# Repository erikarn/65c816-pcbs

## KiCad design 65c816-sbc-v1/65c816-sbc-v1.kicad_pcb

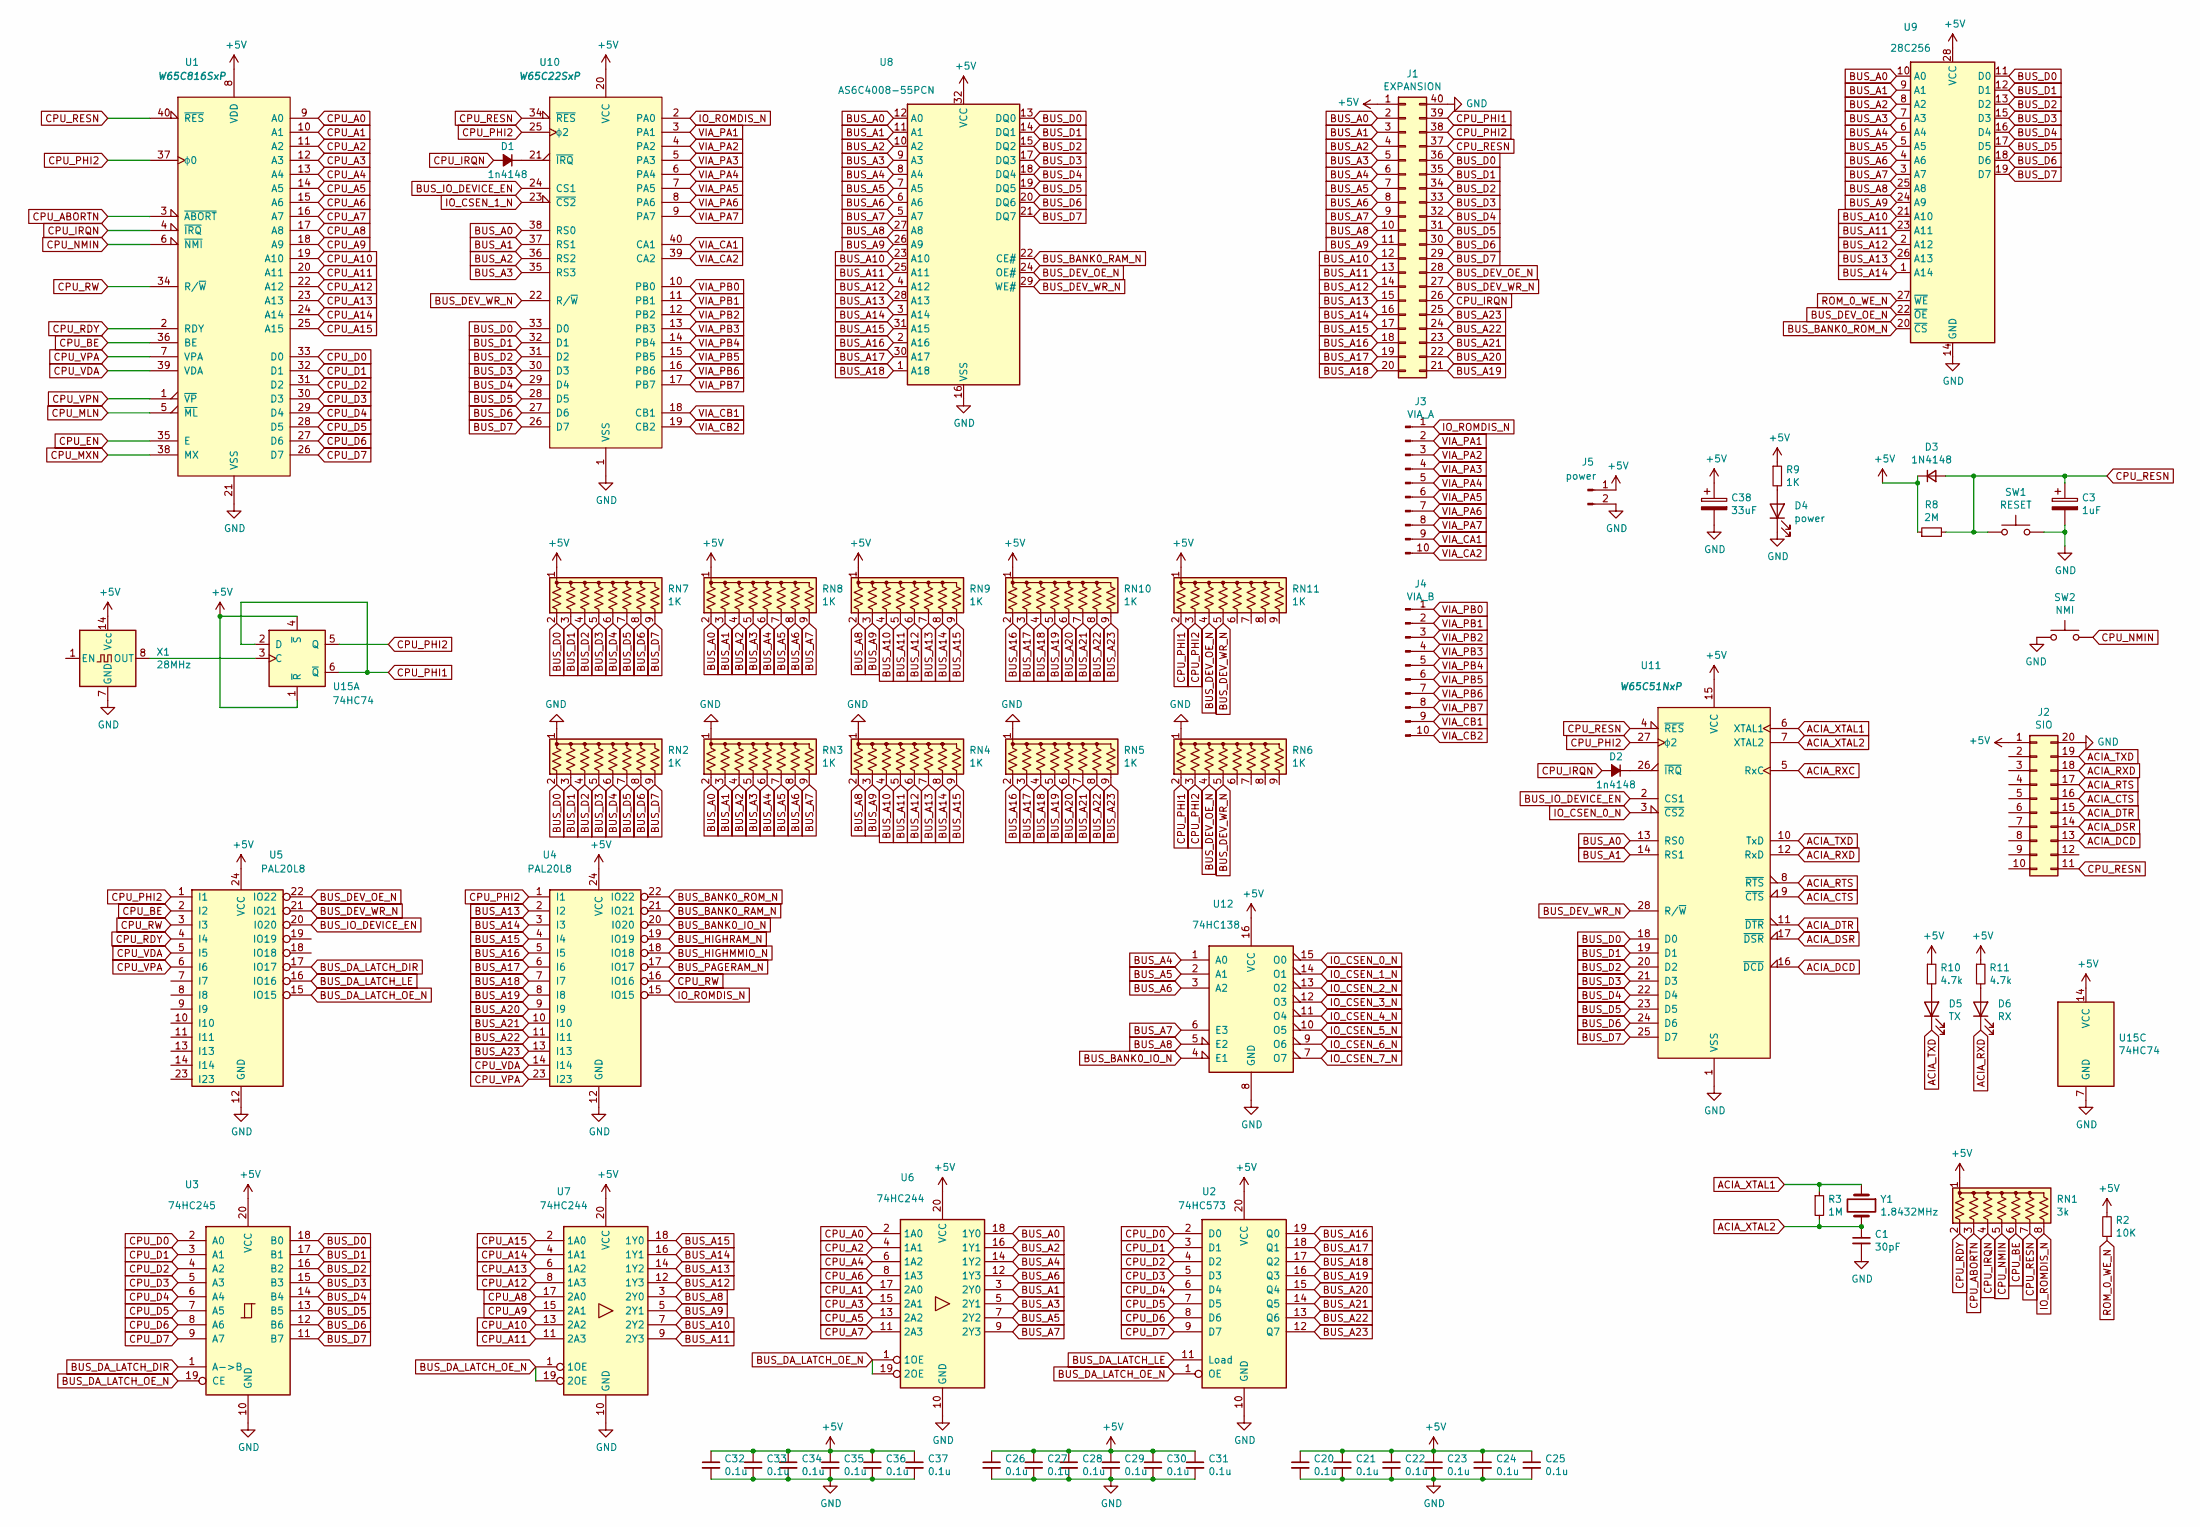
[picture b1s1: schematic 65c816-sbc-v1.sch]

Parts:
C1: 30pF; C_Rect_L4.0mm_W2.5mm_P2.50mm
C3: 1uF; CP_Radial_D6.3mm_P2.50mm
C20, C21, C22, C23, C24, C25, C26, C27, C28, C29, C30, C31, C32, C33, C34, C35, C36, C37: 0.1u; C_Rect_L4.0mm_W2.5mm_P2.50mm
C38: 33uF; CP_Radial_D6.3mm_P2.50mm
D1, D2: 1n4148; D_DO-35_SOD27_P7.62mm_Horizontal
D3: 1N4148; D_DO-35_SOD27_P7.62mm_Horizontal
D4: power; LED_D4.0mm
D5: TX; LED_D4.0mm
D6: RX; LED_D4.0mm
J1: EXPANSION; PinHeader_2x20_P2.54mm_Vertical
J2: SIO; PinHeader_2x10_P2.54mm_Vertical
J3: VIA_A; PinHeader_1x10_P2.54mm_Vertical
J4: VIA_B; PinHeader_1x10_P2.54mm_Vertical
J5: power; PinHeader_1x02_P2.54mm_Vertical
R2: 10K; R_Axial_DIN0207_L6.3mm_D2.5mm_P5.08mm_Vertical
R3: 1M; R_Axial_DIN0207_L6.3mm_D2.5mm_P5.08mm_Vertical
R8: 2M; R_Axial_DIN0207_L6.3mm_D2.5mm_P5.08mm_Vertical
R9: 1K; R_Axial_DIN0207_L6.3mm_D2.5mm_P5.08mm_Vertical
R10, R11: 4.7k; R_Axial_DIN0207_L6.3mm_D2.5mm_P5.08mm_Vertical
RN1: 3k; R_Array_SIP8
RN2, RN3, RN4, RN5, RN6, RN7, RN8, RN9, RN10, RN11: 1K; R_Array_SIP9
SW1: RESET; KSA_Tactile_SPST
SW2: NMI; KSA_Tactile_SPST
U1: W65C816SxP; DIP-40_W15.24mm_Socket
U2: 74HC573; DIP-20_W7.62mm_Socket
U3: 74HC245; DIP-20_W7.62mm_Socket
U4, U5: PAL20L8; DIP-24_W7.62mm_Socket
U6, U7: 74HC244; DIP-20_W7.62mm_Socket
U8: AS6C4008-55PCN; DIP-32_W15.24mm
U9: 28C256; DIP-28_W15.24mm_Socket
U10: W65C22SxP; DIP-40_W15.24mm_Socket
U11: W65C51NxP; DIP-40_W15.24mm_Socket
U12: 74HC138; DIP-16_W7.62mm_Socket
U15: 74HC74; DIP-14_W7.62mm_Socket
X1: 28MHz; Oscillator_DIP-14
Y1: 1.8432MHz; Crystal_HC49-4H_Vertical

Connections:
+5V: C20.1, C21.1, C22.1, C23.1, C24.1, C25.1, C26.1, C27.1, C28.1, C29.1, C30.1, C31.1, C32.1, C33.1, C34.1, C35.1, C36.1, C37.1, C38.1, D3.1 (K), J1.1, J2.1, J5.1, R2.2, R8.1, R9.1, R10.1, R11.1, RN1.1 (common), RN7.1 (common), RN8.1 (common), RN9.1 (common), RN10.1 (common), RN11.1 (common), U1.8 (VDD), U2.20 (VCC), U3.20 (VCC), U4.24 (VCC), U5.24 (VCC), U6.20 (VCC), U7.20 (VCC), U8.32 (VCC), U9.28 (VCC), U10.20 (VCC), U11.15 (VCC), U12.16 (VCC), U15.1 (~R), U15.4 (~S), U15.14 (VCC), X1.14 (Vcc)
ACIA_CTS: J2.16, U11.9 (~CTS)
ACIA_DCD: J2.13, U11.16 (~DCD)
ACIA_DSR: J2.14, U11.17 (~DSR)
ACIA_DTR: J2.15, U11.11 (~DTR)
ACIA_RTS: J2.17, U11.8 (~RTS)
ACIA_RXC: U11.5 (RxC)
ACIA_RXD: D6.1 (K), J2.18, U11.12 (RxD)
ACIA_TXD: D5.1 (K), J2.19, U11.10 (TxD)
ACIA_XTAL1: R3.1, U11.6 (XTAL1), Y1.1
ACIA_XTAL2: C1.1, R3.2, U11.7 (XTAL2), Y1.2
BUS_A0: J1.2, RN3.2 (R1), RN8.2 (R1), U6.18 (1Y0), U8.12 (A0), U9.10 (A0), U10.38 (RS0), U11.13 (RS0)
BUS_A1: J1.3, RN3.3 (R2), RN8.3 (R2), U6.3 (2Y0), U8.11 (A1), U9.9 (A1), U10.37 (RS1), U11.14 (RS1)
BUS_A2: J1.4, RN3.4 (R3), RN8.4 (R3), U6.16 (1Y1), U8.10 (A2), U9.8 (A2), U10.36 (RS2)
BUS_A3: J1.5, RN3.5 (R4), RN8.5 (R4), U6.5 (2Y1), U8.9 (A3), U9.7 (A3), U10.35 (RS3)
BUS_A4: J1.6, RN3.6 (R5), RN8.6 (R5), U6.14 (1Y2), U8.8 (A4), U9.6 (A4), U12.1 (A0)
BUS_A5: J1.7, RN3.7 (R6), RN8.7 (R6), U6.7 (2Y2), U8.7 (A5), U9.5 (A5), U12.2 (A1)
BUS_A6: J1.8, RN3.8 (R7), RN8.8 (R7), U6.12 (1Y3), U8.6 (A6), U9.4 (A6), U12.3 (A2)
BUS_A7: J1.9, RN3.9 (R8), RN8.9 (R8), U6.9 (2Y3), U8.5 (A7), U9.3 (A7), U12.6 (E3)
BUS_A8: J1.10, RN4.2 (R1), RN9.2 (R1), U7.3 (2Y0), U8.27 (A8), U9.25 (A8), U12.5 (E2)
BUS_A9: J1.11, RN4.3 (R2), RN9.3 (R2), U7.5 (2Y1), U8.26 (A9), U9.24 (A9)
BUS_A10: J1.12, RN4.4 (R3), RN9.4 (R3), U7.7 (2Y2), U8.23 (A10), U9.21 (A10)
BUS_A11: J1.13, RN4.5 (R4), RN9.5 (R4), U7.9 (2Y3), U8.25 (A11), U9.23 (A11)
BUS_A12: J1.14, RN4.6 (R5), RN9.6 (R5), U7.12 (1Y3), U8.4 (A12), U9.2 (A12)
BUS_A13: J1.15, RN4.7 (R6), RN9.7 (R6), U4.2 (I2), U7.14 (1Y2), U8.28 (A13), U9.26 (A13)
BUS_A14: J1.16, RN4.8 (R7), RN9.8 (R7), U4.3 (I3), U7.16 (1Y1), U8.3 (A14), U9.1 (A14)
BUS_A15: J1.17, RN4.9 (R8), RN9.9 (R8), U4.4 (I4), U7.18 (1Y0), U8.31 (A15)
BUS_A16: J1.18, RN5.2 (R1), RN10.2 (R1), U2.19 (Q0), U4.5 (I5), U8.2 (A16)
BUS_A17: J1.19, RN5.3 (R2), RN10.3 (R2), U2.18 (Q1), U4.6 (I6), U8.30 (A17)
BUS_A18: J1.20, RN5.4 (R3), RN10.4 (R3), U2.17 (Q2), U4.7 (I7), U8.1 (A18)
BUS_A19: J1.21, RN5.5 (R4), RN10.5 (R4), U2.16 (Q3), U4.8 (I8)
BUS_A20: J1.22, RN5.6 (R5), RN10.6 (R5), U2.15 (Q4), U4.9 (I9)
BUS_A21: J1.23, RN5.7 (R6), RN10.7 (R6), U2.14 (Q5), U4.10 (I10)
BUS_A22: J1.24, RN5.8 (R7), RN10.8 (R7), U2.13 (Q6), U4.11 (I11)
BUS_A23: J1.25, RN5.9 (R8), RN10.9 (R8), U2.12 (Q7), U4.13 (I13)
BUS_BANK0_IO_N: U4.20 (I020), U12.4 (E1)
BUS_BANK0_RAM_N: U4.21 (IO21), U8.22 (CE#)
BUS_BANK0_ROM_N: U4.22 (IO22), U9.20 (~CS)
BUS_D0: J1.36, RN2.2 (R1), RN7.2 (R1), U3.18 (B0), U8.13 (DQ0), U9.11 (D0), U10.33 (D0), U11.18 (D0)
BUS_D1: J1.35, RN2.3 (R2), RN7.3 (R2), U3.17 (B1), U8.14 (DQ1), U9.12 (D1), U10.32 (D1), U11.19 (D1)
BUS_D2: J1.34, RN2.4 (R3), RN7.4 (R3), U3.16 (B2), U8.15 (DQ2), U9.13 (D2), U10.31 (D2), U11.20 (D2)
BUS_D3: J1.33, RN2.5 (R4), RN7.5 (R4), U3.15 (B3), U8.17 (DQ3), U9.15 (D3), U10.30 (D3), U11.21 (D3)
BUS_D4: J1.32, RN2.6 (R5), RN7.6 (R5), U3.14 (B4), U8.18 (DQ4), U9.16 (D4), U10.29 (D4), U11.22 (D4)
BUS_D5: J1.31, RN2.7 (R6), RN7.7 (R6), U3.13 (B5), U8.19 (DQ5), U9.17 (D5), U10.28 (D5), U11.23 (D5)
BUS_D6: J1.30, RN2.8 (R7), RN7.8 (R7), U3.12 (B6), U8.20 (DQ6), U9.18 (D6), U10.27 (D6), U11.24 (D6)
BUS_D7: J1.29, RN2.9 (R8), RN7.9 (R8), U3.11 (B7), U8.21 (DQ7), U9.19 (D7), U10.26 (D7), U11.25 (D7)
BUS_DA_LATCH_DIR: U3.1 (A->B), U5.17 (IO17)
BUS_DA_LATCH_LE: U2.11 (Load), U5.16 (IO16)
BUS_DA_LATCH_OE_N: U2.1 (OE), U3.19 (CE), U5.15 (IO15), U6.1 (1OE), U6.19 (2OE), U7.1 (1OE), U7.19 (2OE)
BUS_DEV_OE_N: J1.28, RN6.4 (R3), RN11.4 (R3), U5.22 (IO22), U8.24 (OE#), U9.22 (~OE)
BUS_DEV_WR_N: J1.27, RN6.5 (R4), RN11.5 (R4), U5.21 (IO21), U8.29 (WE#), U10.22 (R/~W), U11.28 (R/~W)
BUS_HIGHMMIO_N: U4.18 (IO18)
BUS_HIGHRAM_N: U4.19 (IO19)
BUS_IO_DEVICE_EN: U5.20 (I020), U10.24 (CS1), U11.2 (CS1)
BUS_PAGERAM_N: U4.17 (IO17)
CPU_A0: U1.9 (A0), U6.2 (1A0)
CPU_A1: U1.10 (A1), U6.17 (2A0)
CPU_A2: U1.11 (A2), U6.4 (1A1)
CPU_A3: U1.12 (A3), U6.15 (2A1)
CPU_A4: U1.13 (A4), U6.6 (1A2)
CPU_A5: U1.14 (A5), U6.13 (2A2)
CPU_A6: U1.15 (A6), U6.8 (1A3)
CPU_A7: U1.16 (A7), U6.11 (2A3)
CPU_A8: U1.17 (A8), U7.17 (2A0)
CPU_A9: U1.18 (A9), U7.15 (2A1)
CPU_A10: U1.19 (A10), U7.13 (2A2)
CPU_A11: U1.20 (A11), U7.11 (2A3)
CPU_A12: U1.22 (A12), U7.8 (1A3)
CPU_A13: U1.23 (A13), U7.6 (1A2)
CPU_A14: U1.24 (A14), U7.4 (1A1)
CPU_A15: U1.25 (A15), U7.2 (1A0)
CPU_ABORTN: RN1.3 (R2), U1.3 (~ABORT)
CPU_BE: RN1.6 (R5), U1.36 (BE), U5.2 (I2)
CPU_D0: U1.33 (D0), U2.2 (D0), U3.2 (A0)
CPU_D1: U1.32 (D1), U2.3 (D1), U3.3 (A1)
CPU_D2: U1.31 (D2), U2.4 (D2), U3.4 (A2)
CPU_D3: U1.30 (D3), U2.5 (D3), U3.5 (A3)
CPU_D4: U1.29 (D4), U2.6 (D4), U3.6 (A4)
CPU_D5: U1.28 (D5), U2.7 (D5), U3.7 (A5)
CPU_D6: U1.27 (D6), U2.8 (D6), U3.8 (A6)
CPU_D7: U1.26 (D7), U2.9 (D7), U3.9 (A7)
CPU_EN: U1.35 (E)
CPU_IRQN: D1.2 (A), D2.2 (A), J1.26, RN1.4 (R3), U1.4 (~IRQ)
CPU_MLN: U1.5 (~ML)
CPU_MXN: U1.38 (MX)
CPU_NMIN: RN1.5 (R4), SW2.1, U1.6 (~NMI)
CPU_PHI1: J1.39, RN6.2 (R1), RN11.2 (R1), U15.2 (D), U15.6 (~Q)
CPU_PHI2: J1.38, RN6.3 (R2), RN11.3 (R2), U1.37 (ϕ0), U4.1 (I1), U5.1 (I1), U10.25 (ϕ2), U11.27 (ϕ2), U15.5 (Q)
CPU_RDY: RN1.2 (R1), U1.2 (RDY), U5.4 (I4)
CPU_RESN: C3.1, D3.2 (A), J1.37, J2.11, R8.2, RN1.7 (R6), SW1.1, U1.40 (~RES), U10.34 (~RES), U11.4 (~RES)
CPU_RW: U1.34 (R/~W), U4.16 (IO16), U5.3 (I3)
CPU_VDA: U1.39 (VDA), U4.14 (I14), U5.5 (I5)
CPU_VPA: U1.7 (VPA), U4.23 (I23), U5.6 (I6)
CPU_VPN: U1.1 (~VP)
GND: C1.2, C3.2, C20.2, C21.2, C22.2, C23.2, C24.2, C25.2, C26.2, C27.2, C28.2, C29.2, C30.2, C31.2, C32.2, C33.2, C34.2, C35.2, C36.2, C37.2, C38.2, D4.1 (K), J1.40, J2.20, J5.2, RN2.1 (common), RN3.1 (common), RN4.1 (common), RN5.1 (common), RN6.1 (common), SW1.2, SW2.2, U1.21 (VSS), U2.10 (GND), U3.10 (GND), U4.12 (GND), U5.12 (GND), U6.10 (GND), U7.10 (GND), U8.16 (VSS), U9.14 (GND), U10.1 (VSS), U11.1 (VSS), U12.8 (GND), U15.7 (GND), X1.7 (GND)
IO_CSEN_0_N: U11.3 (~CS2), U12.15 (O0)
IO_CSEN_1_N: U10.23 (~CS2), U12.14 (O1)
IO_CSEN_2_N: U12.13 (O2)
IO_CSEN_3_N: U12.12 (O3)
IO_CSEN_4_N: U12.11 (O4)
IO_CSEN_5_N: U12.10 (O5)
IO_CSEN_6_N: U12.9 (O6)
IO_CSEN_7_N: U12.7 (O7)
IO_ROMDIS_N: J3.1, RN1.8 (R7), U4.15 (IO15), U10.2 (PA0)
unnamed: D1.1 (K), U10.21 (~IRQ)
unnamed: D2.1 (K), U11.26 (~IRQ)
unnamed: D4.2 (A), R9.2
unnamed: D5.2 (A), R10.2
unnamed: D6.2 (A), R11.2
unnamed: U15.3 (C), X1.8 (OUT)
ROM_0_WE_N: R2.1, U9.27 (~WE)
VIA_CA1: J3.9, U10.40 (CA1)
VIA_CA2: J3.10, U10.39 (CA2)
VIA_CB1: J4.9, U10.18 (CB1)
VIA_CB2: J4.10, U10.19 (CB2)
VIA_PA1: J3.2, U10.3 (PA1)
VIA_PA2: J3.3, U10.4 (PA2)
VIA_PA3: J3.4, U10.5 (PA3)
VIA_PA4: J3.5, U10.6 (PA4)
VIA_PA5: J3.6, U10.7 (PA5)
VIA_PA6: J3.7, U10.8 (PA6)
VIA_PA7: J3.8, U10.9 (PA7)
VIA_PB0: J4.1, U10.10 (PB0)
VIA_PB1: J4.2, U10.11 (PB1)
VIA_PB2: J4.3, U10.12 (PB2)
VIA_PB3: J4.4, U10.13 (PB3)
VIA_PB4: J4.5, U10.14 (PB4)
VIA_PB5: J4.6, U10.15 (PB5)
VIA_PB6: J4.7, U10.16 (PB6)
VIA_PB7: J4.8, U10.17 (PB7)

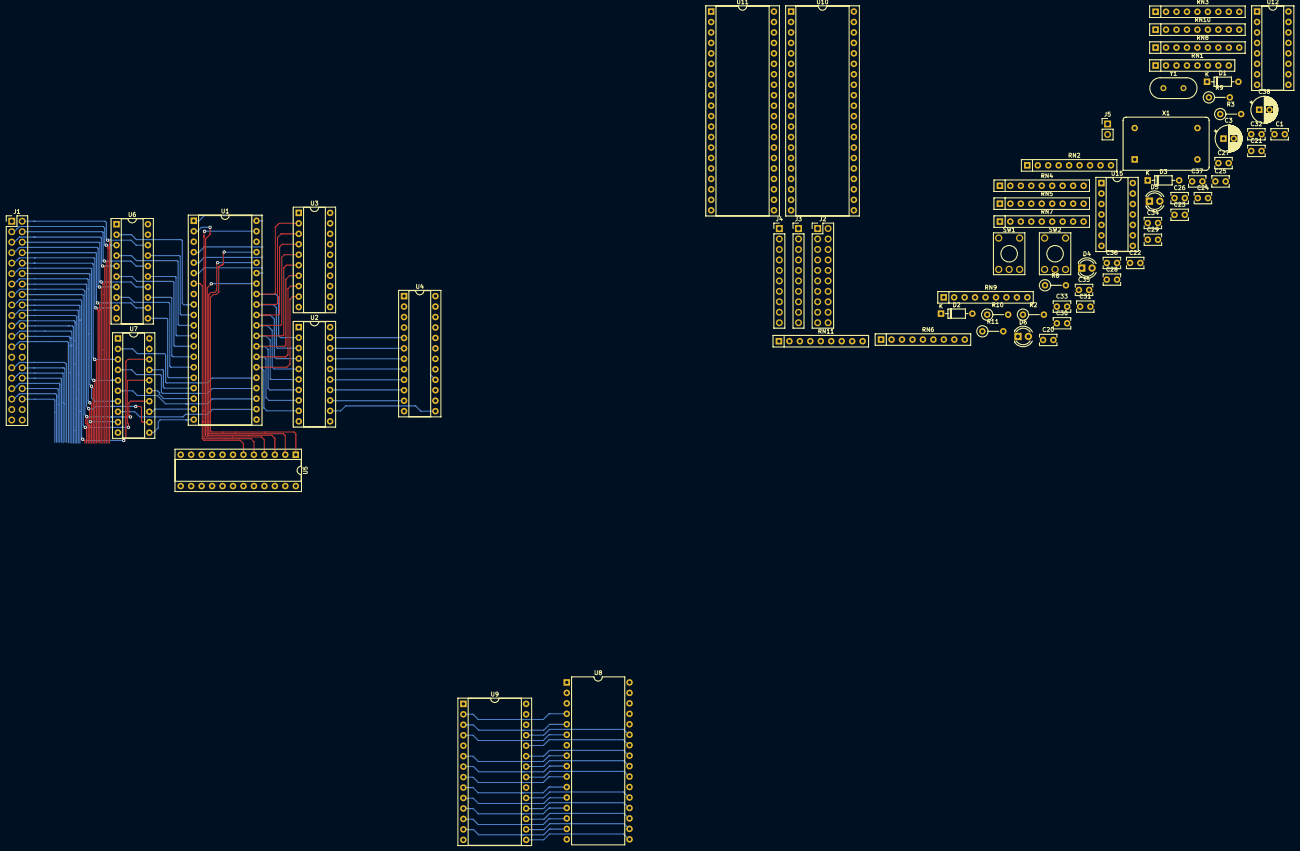
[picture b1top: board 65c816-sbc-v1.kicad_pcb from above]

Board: 4 copper layers, 66 parts (0 on the bottom side), 116 nets.

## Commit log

2021-12-20 initial commit; WIP attempt at a single sheet SBC design
    We'll see how it comes together!
2021-12-20 squeeze in an ACIA too
    It's half done, and I still need to figur eout how to do the two CS'es
    on these peripherals given my current IO decoding scheme.
2021-12-21 Update larger layout, more IO pins defined
    Still need to do clock, reset sequencing, etc.
2021-12-21 starting to play around with buttons
2021-12-21 More routing!
2021-12-27 * update * add some microchip/AVR GAL symbols to maybe start using
2022-01-06 update!
2022-01-06 Add some LEDs, I may want to wire them up to make sure I'm doing the right thing? Dunno yet.
2022-01-07 updates; started routing it
2022-01-15 more layout inspired changes
2022-01-16 update schematic/layout some more; this is quite challenging!
2022-01-18 another update; i'm not liking how this is working out right now.
2022-01-26 ok, let's try again
2022-05-20 [65c816] update board routing.
2022-05-20 ... why am I not tracking this file? anyway, also track this flie
2022-05-21 [65c816] more routing funness
